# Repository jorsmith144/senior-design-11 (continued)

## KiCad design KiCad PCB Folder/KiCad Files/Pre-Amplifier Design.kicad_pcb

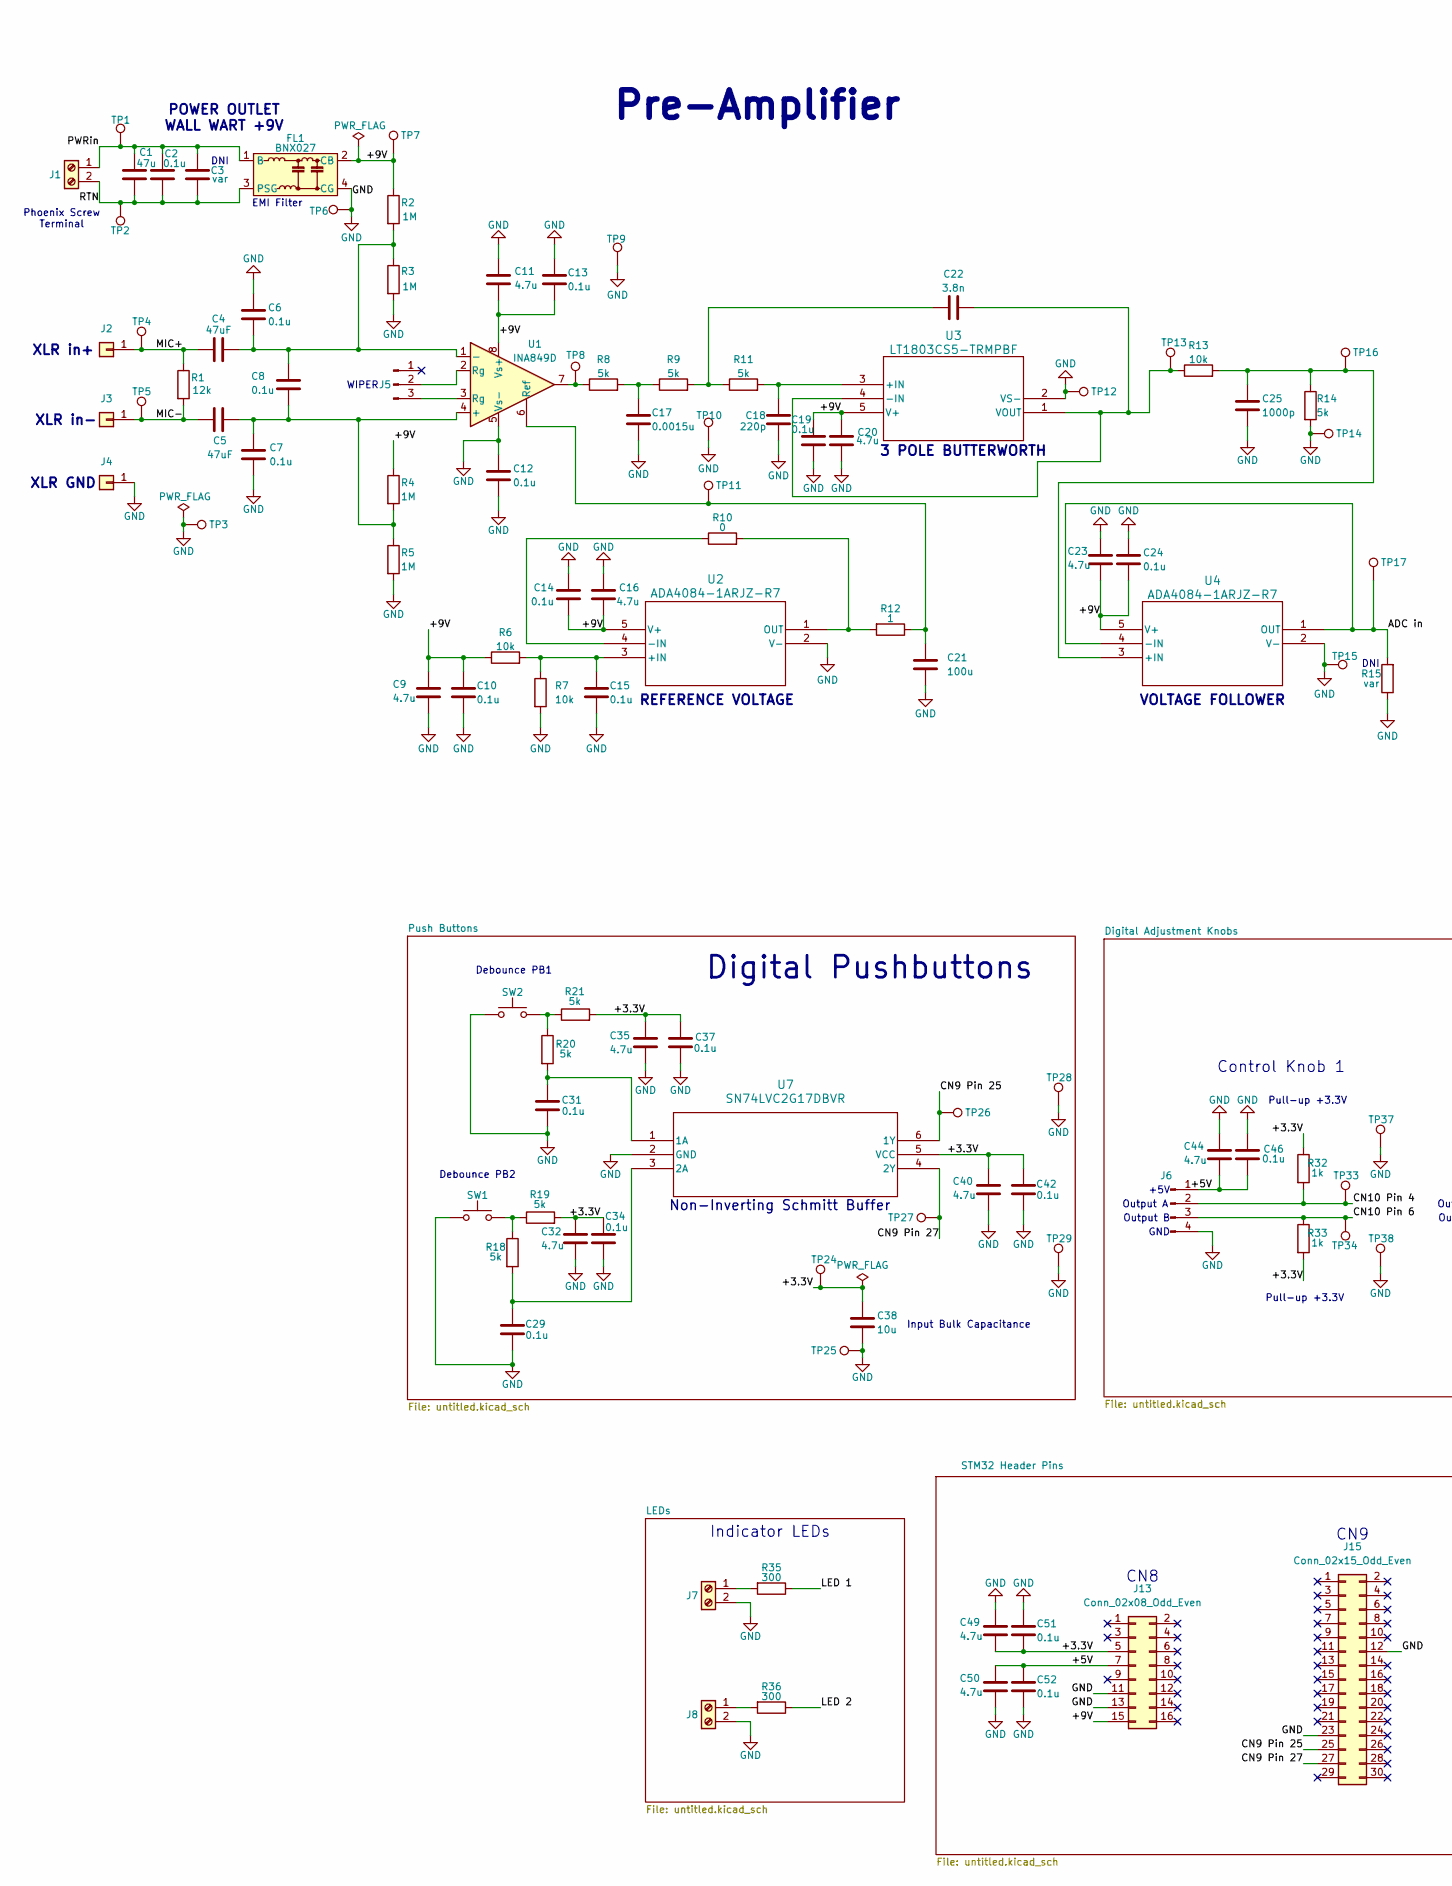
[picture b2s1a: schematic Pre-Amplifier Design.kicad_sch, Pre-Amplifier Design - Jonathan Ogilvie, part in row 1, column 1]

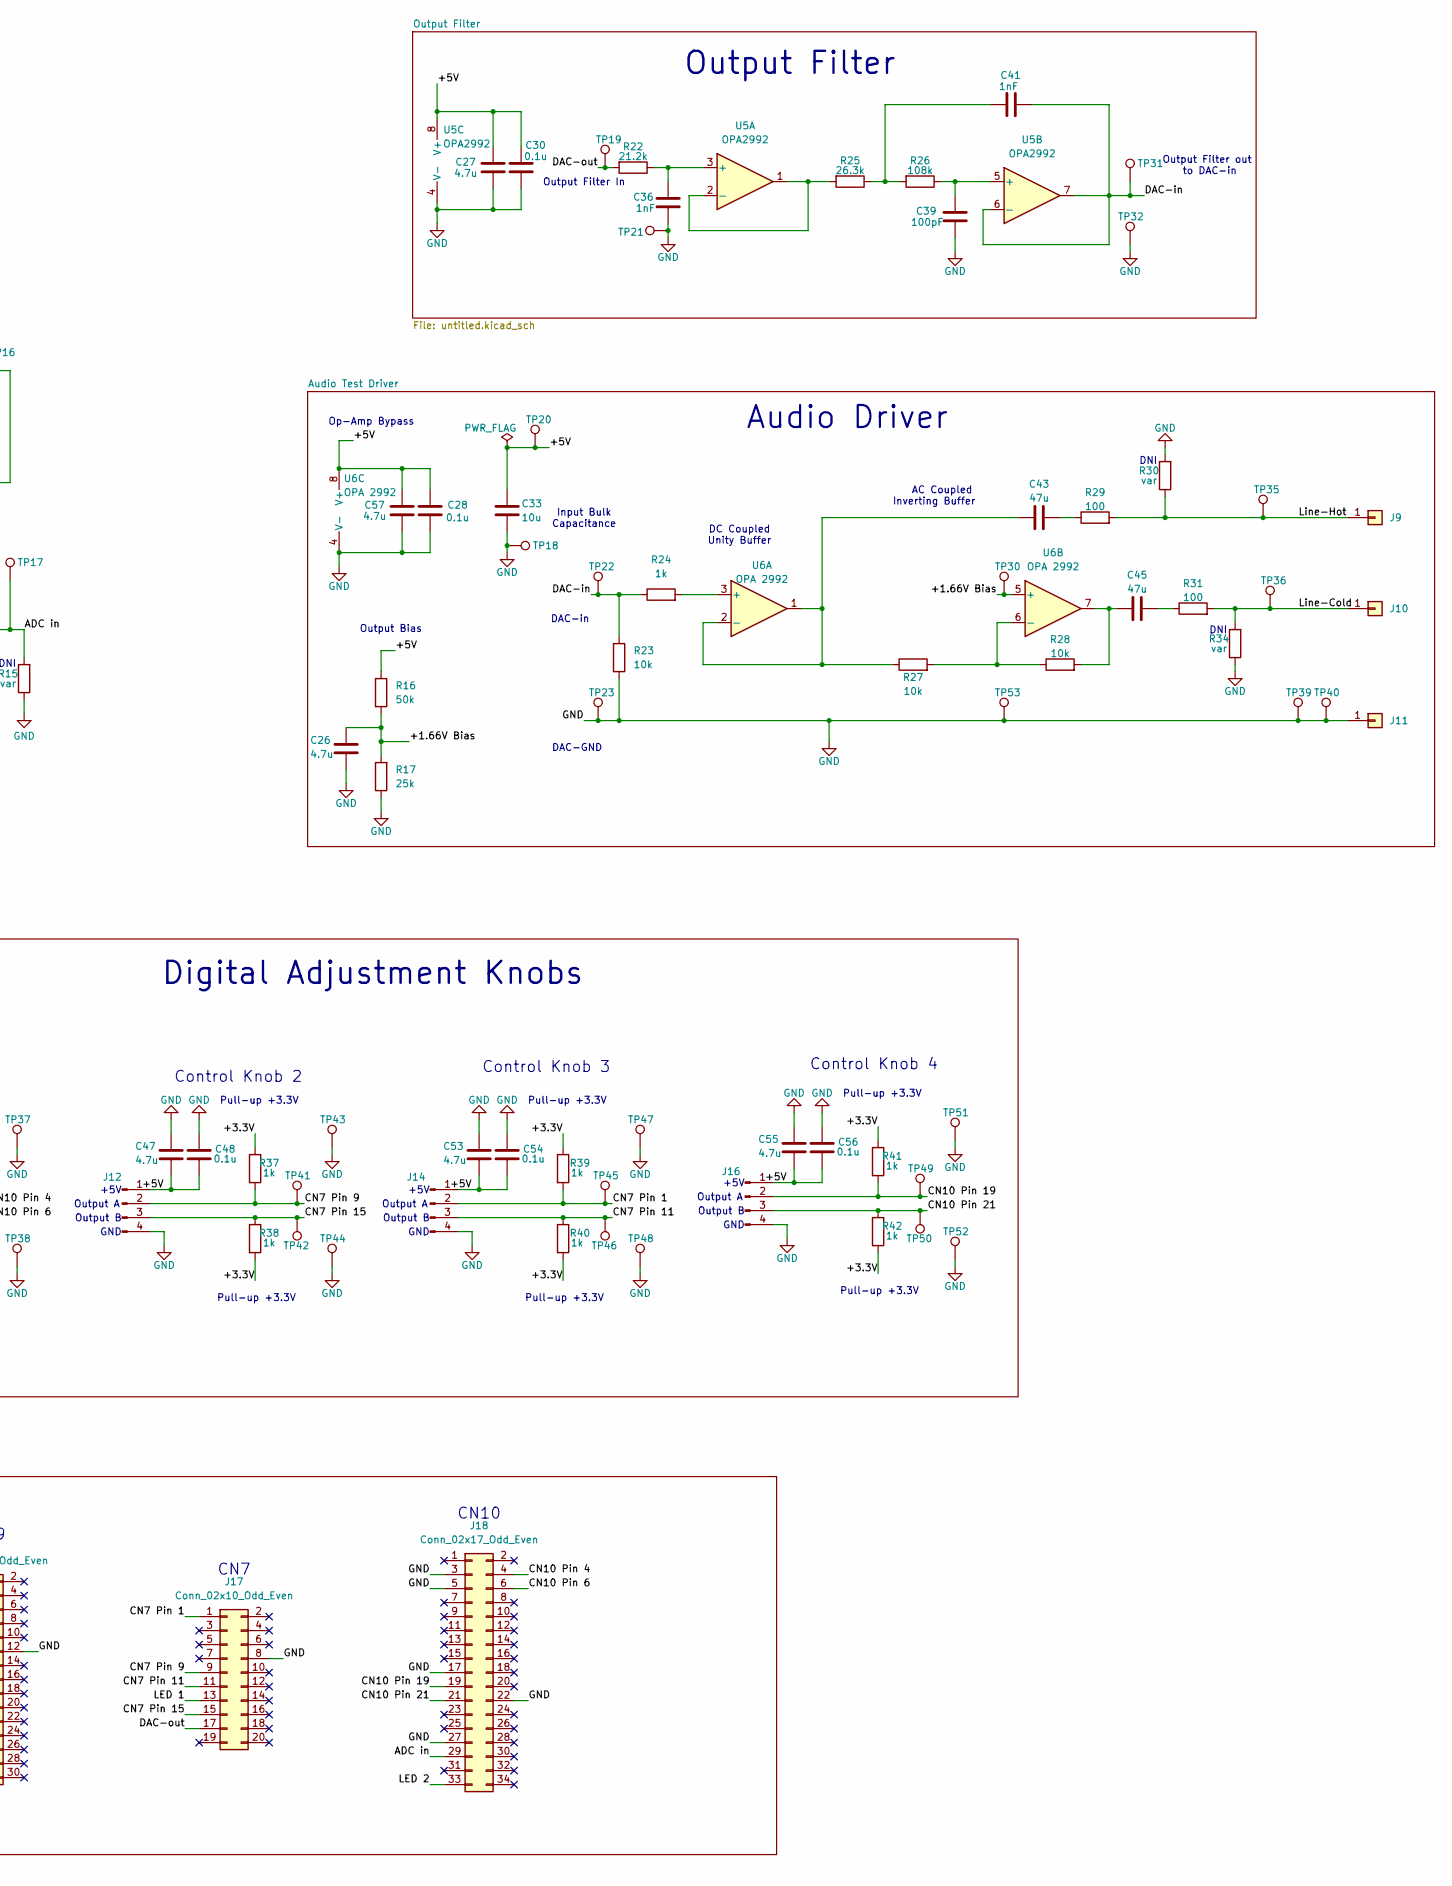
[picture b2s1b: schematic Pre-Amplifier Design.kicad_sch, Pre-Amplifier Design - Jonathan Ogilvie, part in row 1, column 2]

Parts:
C1, C43, C45: 47u; C_1206_3216Metric_Pad1.33x1.80mm_HandSolder
C2, C6, C7, C8, C10, C12, C13, C14, C15, C19, C24, C28, C29, C30, C31, C34, C37, C42, C46, C48, C51, C52, C54, C56: 0.1u; C_0603_1608Metric_Pad1.08x0.95mm_HandSolder
C3: var; C_0603_1608Metric_Pad1.08x0.95mm_HandSolder
C4, C5: 47uF; C_1206_3216Metric_Pad1.33x1.80mm_HandSolder
C9, C11, C16, C20, C23, C26, C27, C32, C35, C40, C44, C47, C49, C50, C53, C55, C57: 4.7u; C_0603_1608Metric_Pad1.08x0.95mm_HandSolder
C17: 0.0015u; C_0603_1608Metric_Pad1.08x0.95mm_HandSolder
C18: 220p; C_0603_1608Metric_Pad1.08x0.95mm_HandSolder
C21: 100u; C_1206_3216Metric_Pad1.33x1.80mm_HandSolder
C22: 3.8n; C_0603_1608Metric_Pad1.08x0.95mm_HandSolder
C25: 1000p; C_0603_1608Metric_Pad1.08x0.95mm_HandSolder
C33, C38: 10u; C_1206_3216Metric_Pad1.33x1.80mm_HandSolder
C36, C41: 1nF; C_0603_1608Metric_Pad1.08x0.95mm_HandSolder
C39: 100pF; C_0603_1608Metric_Pad1.08x0.95mm_HandSolder
FL1: BNX027; Filter_Murata_BNX025
J1, J7, J8: Screw_Terminal_01x02; TerminalBlock_Phoenix_MKDS-1,5-2-5.08_1x02_P5.08mm_Horizont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
J2, J3, J4: Conn_01x01; TestPoint_THTPad_1.5x1.5mm_Drill0.7mm
J5: Conn_01x03_Pin; JST_XH_B3B-XH-A_1x03_P2.50mm_Vertical
J6, J12, J14, J16: Conn_01x04_Pin; Molex_SL_171971-0004_1x04_P2.54mm_Vertical
J9, J10, J11: Conn_01x01; TestPoint_Plated_Hole_D2.0mm
J13: Conn_02x08_Odd_Even; PinHeader_2x08_P2.54mm_Vertical
J15: Conn_02x15_Odd_Even; PinHeader_2x15_P2.54mm_Vertical
J17: Conn_02x10_Odd_Even; PinHeader_2x10_P2.54mm_Vertical
J18: Conn_02x17_Odd_Even; PinHeader_2x17_P2.54mm_Vertical
R1: 12k; R_0603_1608Metric_Pad0.98x0.95mm_HandSolder
R2, R3, R4, R5: 1M; R_0603_1608Metric_Pad0.98x0.95mm_HandSolder
R6, R7, R13, R23, R27, R28: 10k; R_0603_1608Metric_Pad0.98x0.95mm_HandSolder
R8, R9, R11, R14, R18, R19, R20, R21: 5k; R_0603_1608Metric_Pad0.98x0.95mm_HandSolder
R10: 0; R_0603_1608Metric_Pad0.98x0.95mm_HandSolder
R12: 1; R_0603_1608Metric_Pad0.98x0.95mm_HandSolder
R15, R30, R34: var; R_0603_1608Metric_Pad0.98x0.95mm_HandSolder
R16: 50k; R_0603_1608Metric_Pad0.98x0.95mm_HandSolder
R17: 25k; R_0603_1608Metric_Pad0.98x0.95mm_HandSolder
R22: 21.2k; R_0603_1608Metric_Pad0.98x0.95mm_HandSolder
R24, R32, R33, R37, R38, R39, R40, R41, R42: 1k; R_0603_1608Metric_Pad0.98x0.95mm_HandSolder
R25: 26.3k; R_0603_1608Metric_Pad0.98x0.95mm_HandSolder
R26: 108k; R_0603_1608Metric_Pad0.98x0.95mm_HandSolder
R29, R31: 100; R_0603_1608Metric_Pad0.98x0.95mm_HandSolder
R35, R36: 300; R_0603_1608Metric_Pad0.98x0.95mm_HandSolder
SW1, SW2: SW_Push; TerminalBlock_Phoenix_MKDS-1,5-2-5.08_1x02_P5.08mm_Horizont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
TP1, TP2: TestPoint; TestPoint_Plated_Hole_D3.0mm
TP3, TP4, TP5, TP6, TP7, TP8, TP9, TP10, TP11, TP12, TP13, TP14, TP15, TP16, TP17, TP18, TP19, TP20, TP21, TP22, TP23, TP24, TP25, TP26, TP27, TP28, TP29, TP30, TP31, TP32, TP33, TP34, TP35, TP36, TP37, TP38, TP39, TP40, TP41, TP42, TP43, TP44, TP45, TP46, TP47, TP48, TP49, TP50, TP51, TP52, TP53: TestPoint; TestPoint_Keystone_5005-5009_Compact
U1: INA849D; SOIC-8_3.9x4.9mm_P1.27mm
U2, U4: ADA4084-1ARJZ-R7; SOT-23-5_HandSoldering
U3: LT1803CS5-TRMPBF; SOT-23-5_HandSoldering
U5: OPA2992; SOIC-8_3.9x4.9mm_P1.27mm
U6: OPA 2992; SOIC-8_3.9x4.9mm_P1.27mm
U7: SN74LVC2G17DBVR; SOT-23-6_Handsoldering

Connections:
/+1.66V Bias: C26.1, R16.2, R17.2, TP30.1, U6.5 (+)
/+3.3V: C32.1, C34.2, C35.1, C37.1, C38.1, C40.1, C42.2, C49.2, C51.2, J13.5, R19.2, R21.2, R32.1, R33.2, R37.1, R38.2, R39.1, R40.2, R41.1, R42.2, TP24.1, U7.5 (VCC)
/+5V: C27.2, C28.1, C30.2, C33.1, C44.2, C46.2, C47.2, C48.2, C50.1, C52.1, C53.2, C54.2, C55.2, C56.2, C57.2, J6.1, J12.1, J13.7, J14.1, J16.1, R16.1, TP20.1, U5.8 (V+), U6.8 (V+)
/+9V: C9.1, C10.1, C11.2, C13.2, C14.1, C16.1, C19.2, C20.1, C23.2, C24.2, FL1.2 (CB), J13.15, R2.1, R4.1, R6.1, TP7.1, U1.8 (Vs+), U2.5 (V+), U3.5 (V+), U4.5 (V+)
/ADC in: J18.29, R15.2, TP17.1, U4.1 (OUT), U4.4 (-IN)
/CN7 Pin 1: J14.2, J17.1, R39.2, TP45.1
/CN7 Pin 9: J12.2, J17.9, R37.2, TP41.1
/CN7 Pin 11: J14.3, J17.11, R40.1, TP46.1
/CN7 Pin 15: J12.3, J17.15, R38.1, TP42.1
/CN9 Pin 25: J15.25, TP26.1, U7.6 (1Y)
/CN9 Pin 27: J15.27, TP27.1, U7.4 (2Y)
/CN10 Pin 4: J6.2, J18.4, R32.2, TP33.1
/CN10 Pin 6: J6.3, J18.6, R33.1, TP34.1
/CN10 Pin 19: J16.2, J18.19, R41.2, TP49.1
/CN10 Pin 21: J16.3, J18.21, R42.1, TP50.1
/DAC-in: C41.1, R23.1, R24.1, TP22.1, TP31.1, U5.6 (-), U5.7
/DAC-out: J17.17, R22.2, TP19.1
/LED 1: J17.13, R35.1
/LED 2: J18.33, R36.1
/Line-Cold: J10.1, R31.2, R34.2, TP36.1
/Line-Hot: J9.1, R29.2, R30.1, TP35.1
/MIC+: C4.1, J2.1, R1.1, TP4.1
/MIC-: C5.1, J3.1, R1.2, TP5.1
/PWRin: C1.1, C2.1, C3.1, FL1.1 (B), J1.1, TP1.1
/RTN: C1.2, C2.2, C3.2, FL1.3 (PSG), J1.2, TP2.1
GND: C6.1, C7.2, C9.2, C10.2, C11.1, C12.1, C12.2, C13.1, C14.2, C15.2, C16.2, C17.2, C18.2, C19.1, C20.2, C21.2, C23.1, C24.1, C25.2, C26.2, C27.1, C28.2, C29.1, C30.1, C31.1, C32.2, C33.2, C34.1, C35.2, C36.1, C37.2, C38.2, C39.1, C40.2, C42.1, C44.1, C46.1, C47.1, C48.1, C49.1, C50.2, C51.1, C52.2, C53.1, C54.1, C55.1, C56.1, C57.1, FL1.4 (CG), J4.1, J6.4, J7.2, J8.2, J11.1, J12.4, J13.11, J13.13, J14.4, J15.12, J15.23, J16.4, J17.8, J18.3, J18.5, J18.17, J18.22, J18.27, R3.2, R5.2, R7.2, R14.2, R15.1, R17.1, R23.2, R30.2, R34.1, SW1.1, SW2.1, TP3.1, TP6.1, TP9.1, TP10.1, TP12.1, TP14.1, TP15.1, TP18.1, TP21.1, TP23.1, TP25.1, TP28.1, TP29.1, TP32.1, TP37.1, TP38.1, TP39.1, TP40.1, TP43.1, TP44.1, TP47.1, TP48.1, TP51.1, TP52.1, TP53.1, U1.5 (Vs-), U2.2 (V-), U3.2 (VS-), U4.2 (V-), U5.4 (V-), U6.4 (V-), U7.2 (GND)
unnamed: C17.1, R8.2, R9.1
unnamed: C22.1, R9.2, R11.1
unnamed: C41.2, R25.1, R26.2
unnamed: C43.2, R29.1
unnamed: C45.1, R28.2, U6.7
unnamed: C45.2, R31.1
unnamed: J5.2, U1.2 (Rg)
unnamed: J5.3, U1.3 (Rg)
unnamed: J7.1, R35.2
unnamed: J8.1, R36.2
unnamed: R8.1, TP8.1, U1.7
unnamed: R18.1, R19.1, SW1.2
unnamed: R20.1, R21.1, SW2.2
unnamed: C5.2, C7.1, C8.2, R4.2, R5.1, U1.4 (+)
unnamed: C4.2, C6.2, C8.1, R2.2, R3.1, U1.1 (-)
unnamed: C21.1, R12.1, TP11.1, U1.6 (Ref)
unnamed: C15.1, R6.2, R7.1, U2.3 (+IN)
unnamed: R10.1, U2.4 (-IN)
unnamed: R10.2, R12.2, U2.1 (OUT)
unnamed: C18.1, R11.2, U3.3 (+IN)
unnamed: C22.2, R13.1, TP13.1, U3.1 (VOUT), U3.4 (-IN)
unnamed: C25.1, R13.2, R14.1, TP16.1, U4.3 (+IN)
unnamed: C36.2, R22.1, U5.3 (+)
unnamed: R25.2, U5.1, U5.2 (-)
unnamed: C39.2, R26.1, U5.5 (+)
unnamed: R24.2, U6.3 (+)
unnamed: C43.1, R27.1, U6.1, U6.2 (-)
unnamed: R27.2, R28.1, U6.6 (-)
unnamed: C31.2, R20.2, U7.1 (1A)
unnamed: C29.2, R18.2, U7.3 (2A)

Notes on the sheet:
Output A
Pull-up +3.3V
EMI Filter
DNI
CN8
DAC-in
CN9
Non-Inverting Schmitt Buffer
+5V
XLR in+
Debounce PB1
XLR in-
Output B
CN10
DAC-GND
WIPER
GND
Input Bulk Capacitance
Digital Pushbuttons
REFERENCE VOLTAGE
Control Knob 4
Output Bias
AC Coupled Inverting Buffer
POWER OUTLET WALL WART +9V
Digital Adjustment Knobs
Audio Driver
Output Filter In
Input Bulk Capacitance
CN7
DC Coupled Unity Buffer
3 POLE BUTTERWORTH
Output Filter
Op-Amp Bypass
Debounce PB2
Output Filter out to DAC-in
Control Knob 2
XLR GND
Phoenix Screw Terminal
Pre-Amplifier
Control Knob 1

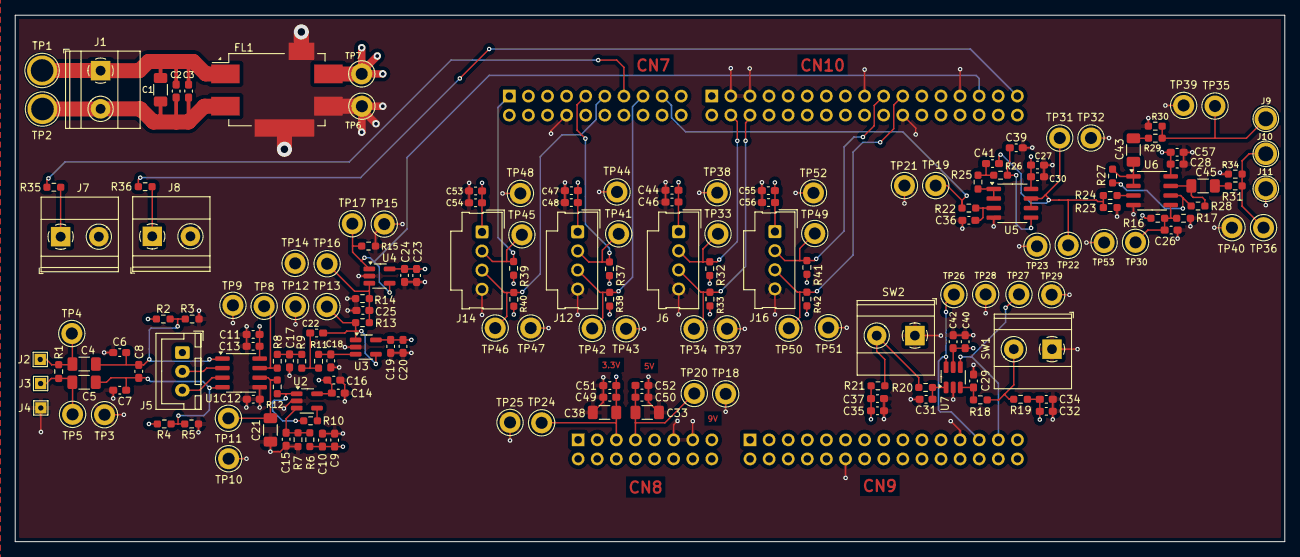
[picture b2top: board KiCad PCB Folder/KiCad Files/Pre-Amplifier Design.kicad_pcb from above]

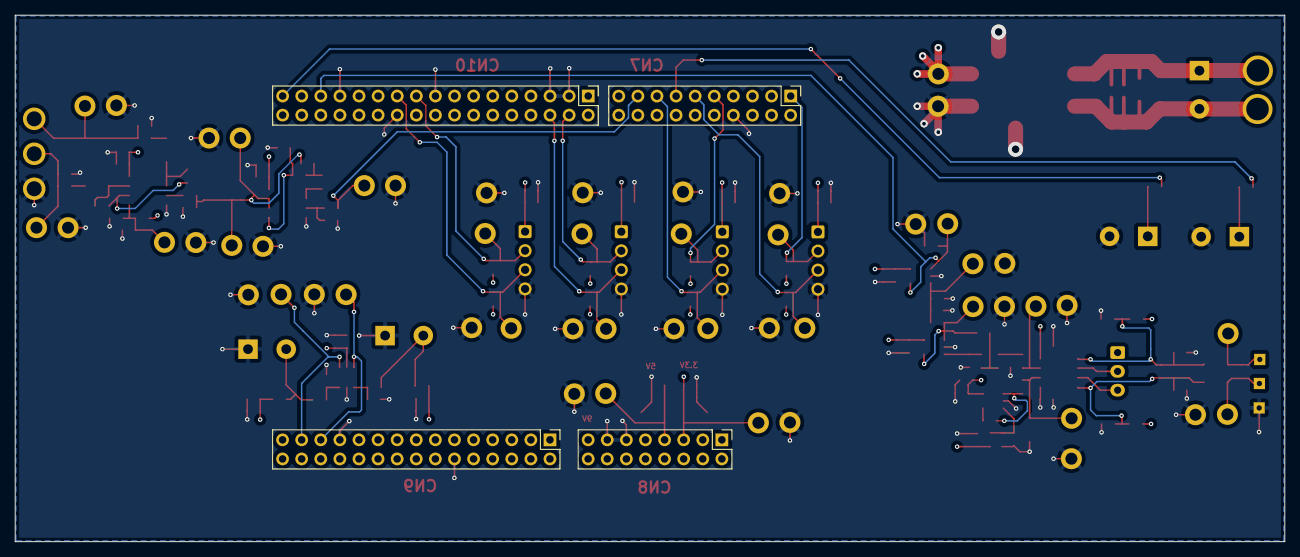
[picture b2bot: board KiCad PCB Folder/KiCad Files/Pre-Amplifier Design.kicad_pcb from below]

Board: 4 copper layers, 168.8 x 70.0 mm, 180 parts (4 on the bottom side), 56 nets.

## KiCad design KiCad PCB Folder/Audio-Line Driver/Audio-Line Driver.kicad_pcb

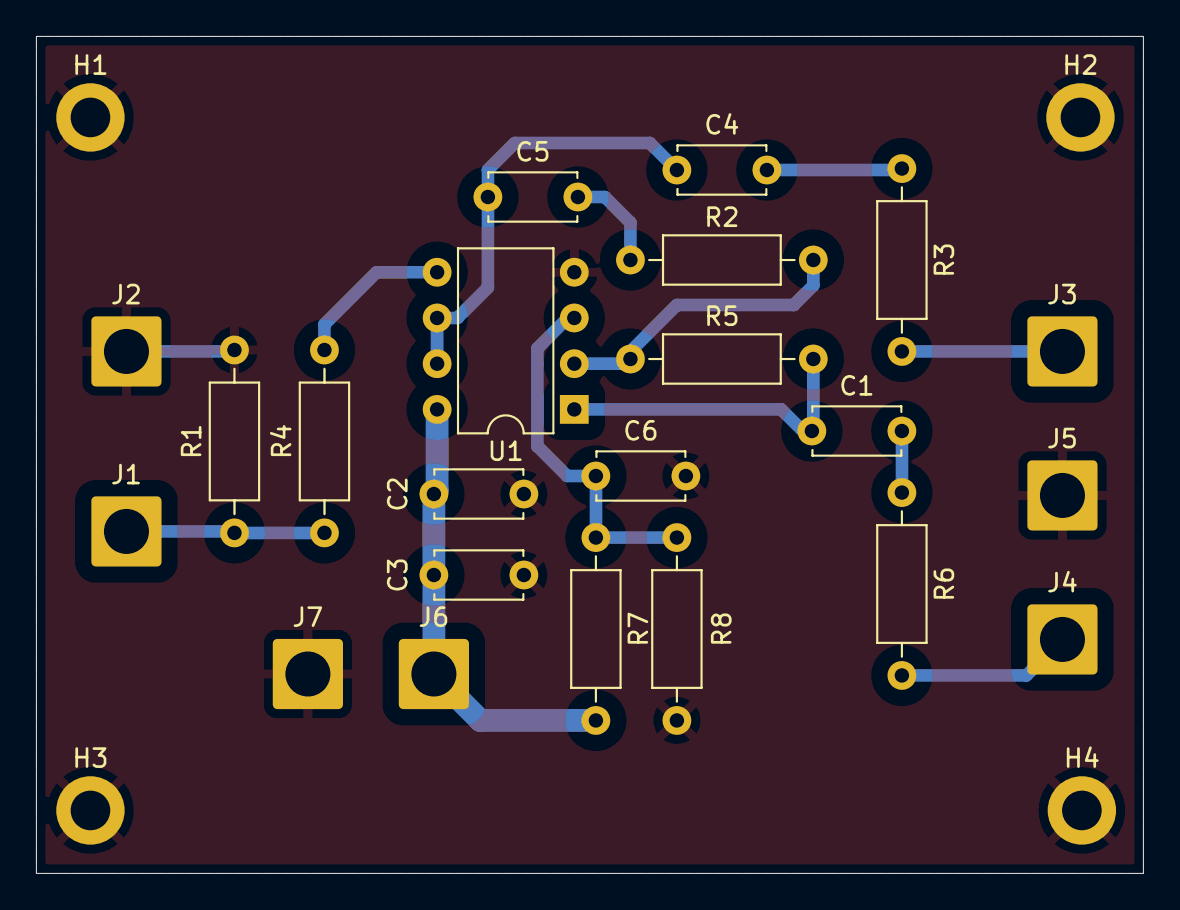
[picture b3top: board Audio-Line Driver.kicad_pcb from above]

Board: 2 copper layers, 61.5 x 46.5 mm, 26 parts (0 on the bottom side), 13 nets.

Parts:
C1, C4: 47uF; C_Disc_D4.7mm_W2.5mm_P5.00mm
C2: 100nF; C_Disc_D4.7mm_W2.5mm_P5.00mm
C3: 100uF; C_Disc_D4.7mm_W2.5mm_P5.00mm
C5: 1uF; C_Disc_D4.7mm_W2.5mm_P5.00mm
C6: 4.7uF; C_Disc_D4.7mm_W2.5mm_P5.00mm
H1, H2, H3, H4: MountingHole_Pad; MountingHole_2.2mm_M2_DIN965_Pad
J1: DAC-Input; SolderWire-2sqmm_1x01_D2mm_OD3.9mm
J2: DAC-GND; SolderWire-2sqmm_1x01_D2mm_OD3.9mm
J3: Line-Hot; SolderWire-2sqmm_1x01_D2mm_OD3.9mm
J4: Line-Cold; SolderWire-2sqmm_1x01_D2mm_OD3.9mm
J5: Line-GND; SolderWire-2sqmm_1x01_D2mm_OD3.9mm
J6: PWR-INPUT; SolderWire-2sqmm_1x01_D2mm_OD3.9mm
J7: PWR-GND; SolderWire-2sqmm_1x01_D2mm_OD3.9mm
R1: 10K; R_Axial_DIN0207_L6.3mm_D2.5mm_P10.16mm_Horizontal
R2, R5: 25K; R_Axial_DIN0207_L6.3mm_D2.5mm_P10.16mm_Horizontal
R3, R6: 100; R_Axial_DIN0207_L6.3mm_D2.5mm_P10.16mm_Horizontal
R4: 1K; R_Axial_DIN0207_L6.3mm_D2.5mm_P10.16mm_Horizontal
R7, R8: 50K; R_Axial_DIN0207_L6.3mm_D2.5mm_P10.16mm_Horizontal
U1: LM358; DIP-8_W7.62mm

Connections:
BIAS 2.5V: C6.1, R7.1, R8.2, U1.3 (+)
GND: C2.2, C3.2, C6.2, H1.1, H2.1, H3.1, H4.1, J2.1, J5.1, J7.1, R1.2, R8.1, U1.4 (V-)
unnamed: C1.1, R5.2, U1.1
unnamed: C1.2, R6.1
unnamed: C4.2, R3.1
unnamed: C5.2, R2.1
unnamed: J1.1, R1.1, R4.1
unnamed: J3.1, R3.2
unnamed: J4.1, R6.2
unnamed: R2.2, R5.1, U1.2 (-)
unnamed: R4.2, U1.5 (+)
unnamed: C4.1, C5.1, U1.6 (-), U1.7
PWR_5V: C2.1, C3.1, J6.1, R7.2, U1.8 (V+)

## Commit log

2024-10-08 test webhook
2024-10-22 KiCad Added
    Added Library and Test Schematic for KiCad
2024-10-22 Test
2024-11-05 STM32 ADC Code
    ADC Is triggered using Timer 8 Interrupt, not sure what my exact sample frequency is. Would need to test.
2024-11-05 Deleted KiCad test stuff
2024-11-06 ADC 48KHz
    Code from lab test today, UART is commented out as it kills the speed.
2025-02-10 this is our update main.c
2025-02-23 Matlab Reverb Code
    Reverb code in Matlab
2025-02-24 Peak, HPF, LPF, Notch, and Reverb All in 1
2025-03-02 filters with reverb, toggle / switching
    this code contains 4 filters, HP, LP, Notch, and peaking as well as reverb. There is also some code of switching and toggling (still has some bugs)
2025-03-05 Create KiCadPCB files
2025-03-05 KiCad PCB Folder
2025-03-05 PCB Project Directory
2025-03-05 AUDIO BALANCED DRIVER BRUNO BOARD
2025-05-16 Create hi
2025-05-16 Create hiPCB
